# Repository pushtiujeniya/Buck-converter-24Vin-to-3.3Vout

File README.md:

# Buck converter of 24Vin DC votlage to 3.3Vout DC  voltage
This repository contain the circuit diagram of buck converter which convert the 24v input dc voltage to 3.3v dc output voltage by using AP64501SP ic.

## Hardware specification
- AP64501SP ic
- input decoupling capacitors for stable dc input voltage
- SMBJ36A diode
- onboard 2 pin header connector for input  voltage and output voltage connection
- Feedback resistors
- Output capacitors

## software 
- kicad 9.0

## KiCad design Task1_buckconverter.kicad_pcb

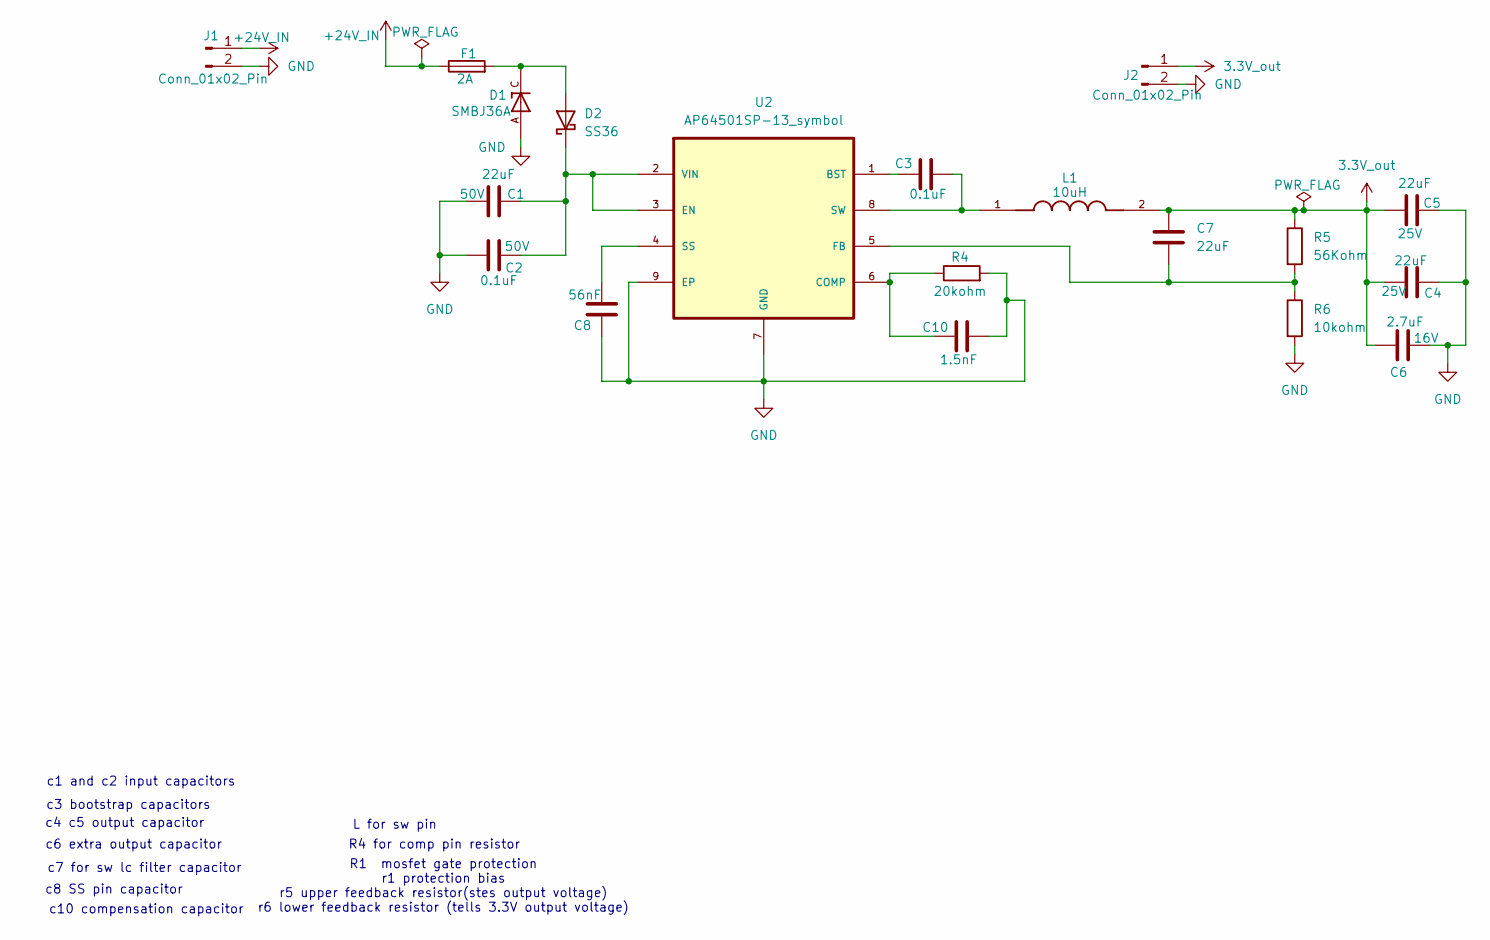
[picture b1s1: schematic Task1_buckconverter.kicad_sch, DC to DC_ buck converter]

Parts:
C1: 22uF; C_Elec_6.3x5.4; voltage 50V
C2, C3: 0.1uF; C_0603_1608Metric; voltage 50V
C4: 22uF; C_0805_2012Metric; voltage 25V
C5: 22uF; C_0805_2012Metric; Voltage 25V; voltage 25V
C6: 2.7uF; C_0603_1608Metric_Pad1.08x0.95mm_HandSolder; voltage 16V
C7: 22uF; C_0603_1608Metric_Pad1.08x0.95mm_HandSolder
C8: 56nF; C_0603_1608Metric_Pad1.08x0.95mm_HandSolder
C10: 1.5nF; C_0603_1608Metric_Pad1.08x0.95mm_HandSolder
D1: SMBJ36A; DIOM4336X265N; PARTREV F2102
D2: SS36; D_SMA
F1: 2A; Fuse_1206_3216Metric
J1, J2: Conn_01x02_Pin; Molex_KK-254_AE-6410-02A_1x02_P2.54mm_Vertical
L1: 10uH; IND_B82464P4474M000; PARTREV 2018-10
R4: 20kohm; R_0603_1608Metric
R5: 56Kohm; R_0603_1608Metric
R6: 10kohm; R_0603_1608Metric
U2: AP64501SP-13_symbol; SOIC127P600X170-9N

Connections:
3.3V_out: C4.1, C5.2, C6.1, C7.1, J2.1, L1.2, R5.1
+24V_IN: F1.1, J1.1
GND: C1.2, C2.2, C4.2, C5.1, C6.2, C8.2, C10.2, D1.A, J1.2, J2.2, R4.2, R6.2, U2.7 (GND), U2.9 (EP)
unnamed: D1.C, D2.2 (A), F1.2
unnamed: C1.1, C2.1, D2.1 (K), U2.2 (VIN), U2.3 (EN)
unnamed: C3.1, U2.1 (BST)
unnamed: C10.1, R4.1, U2.6 (COMP)
unnamed: C7.2, R5.2, R6.1, U2.5 (FB)
unnamed: C8.1, U2.4 (SS)
unnamed: C3.2, L1.1, U2.8 (SW)

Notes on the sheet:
c4 c5 output capacitor
c10 compensation capacitor
R1 mosfet gate protection r1 protection bias r5 upper feedback resistor(stes output voltage) r6 lower feedback resistor (tells 3.3V output voltage)
L for sw pin
c3 bootstrap capacitors
c6 extra output capacitor
c1 and c2 input capacitors
c7 for sw lc filter capacitor
R4 for comp pin resistor
c8 SS pin capacitor

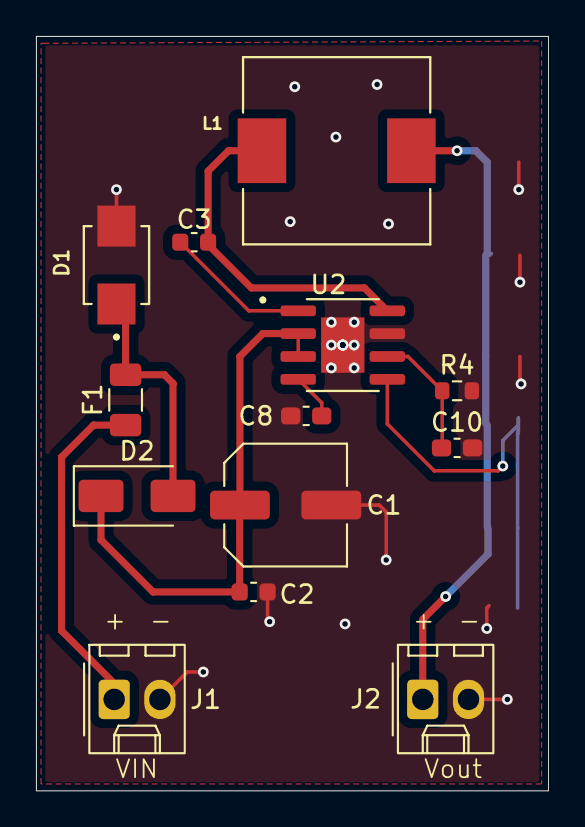
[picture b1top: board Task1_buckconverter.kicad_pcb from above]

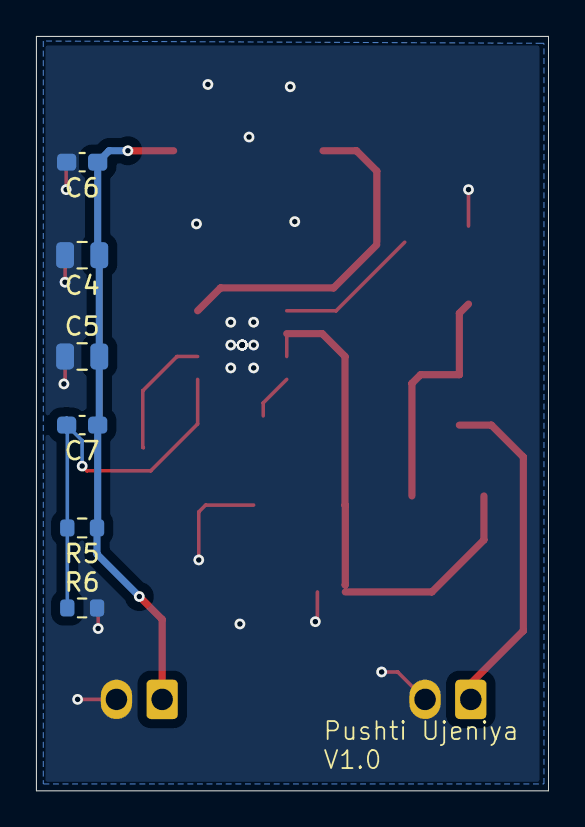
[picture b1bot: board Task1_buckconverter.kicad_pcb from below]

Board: 2 copper layers, 28.4 x 41.9 mm, 19 parts (6 on the bottom side), 10 nets.

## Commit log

2026-04-19 Add temp file in 3D views directory
2026-04-19 3D view images added
2026-04-19 schematic pdf file added
2026-04-19 layout pdf file added
2026-04-19 buck converter files added
2026-04-19 Add temp file to Backup directory
2026-04-19 backup files added
2026-04-19 Add temporary file to external library
2026-04-19 external library of AP60501SP buck converter ic
2026-04-19 Initialize README for buck converter project
    Add README with project overview and specifications
2026-04-19 AP64501SP-13 3d step file added
